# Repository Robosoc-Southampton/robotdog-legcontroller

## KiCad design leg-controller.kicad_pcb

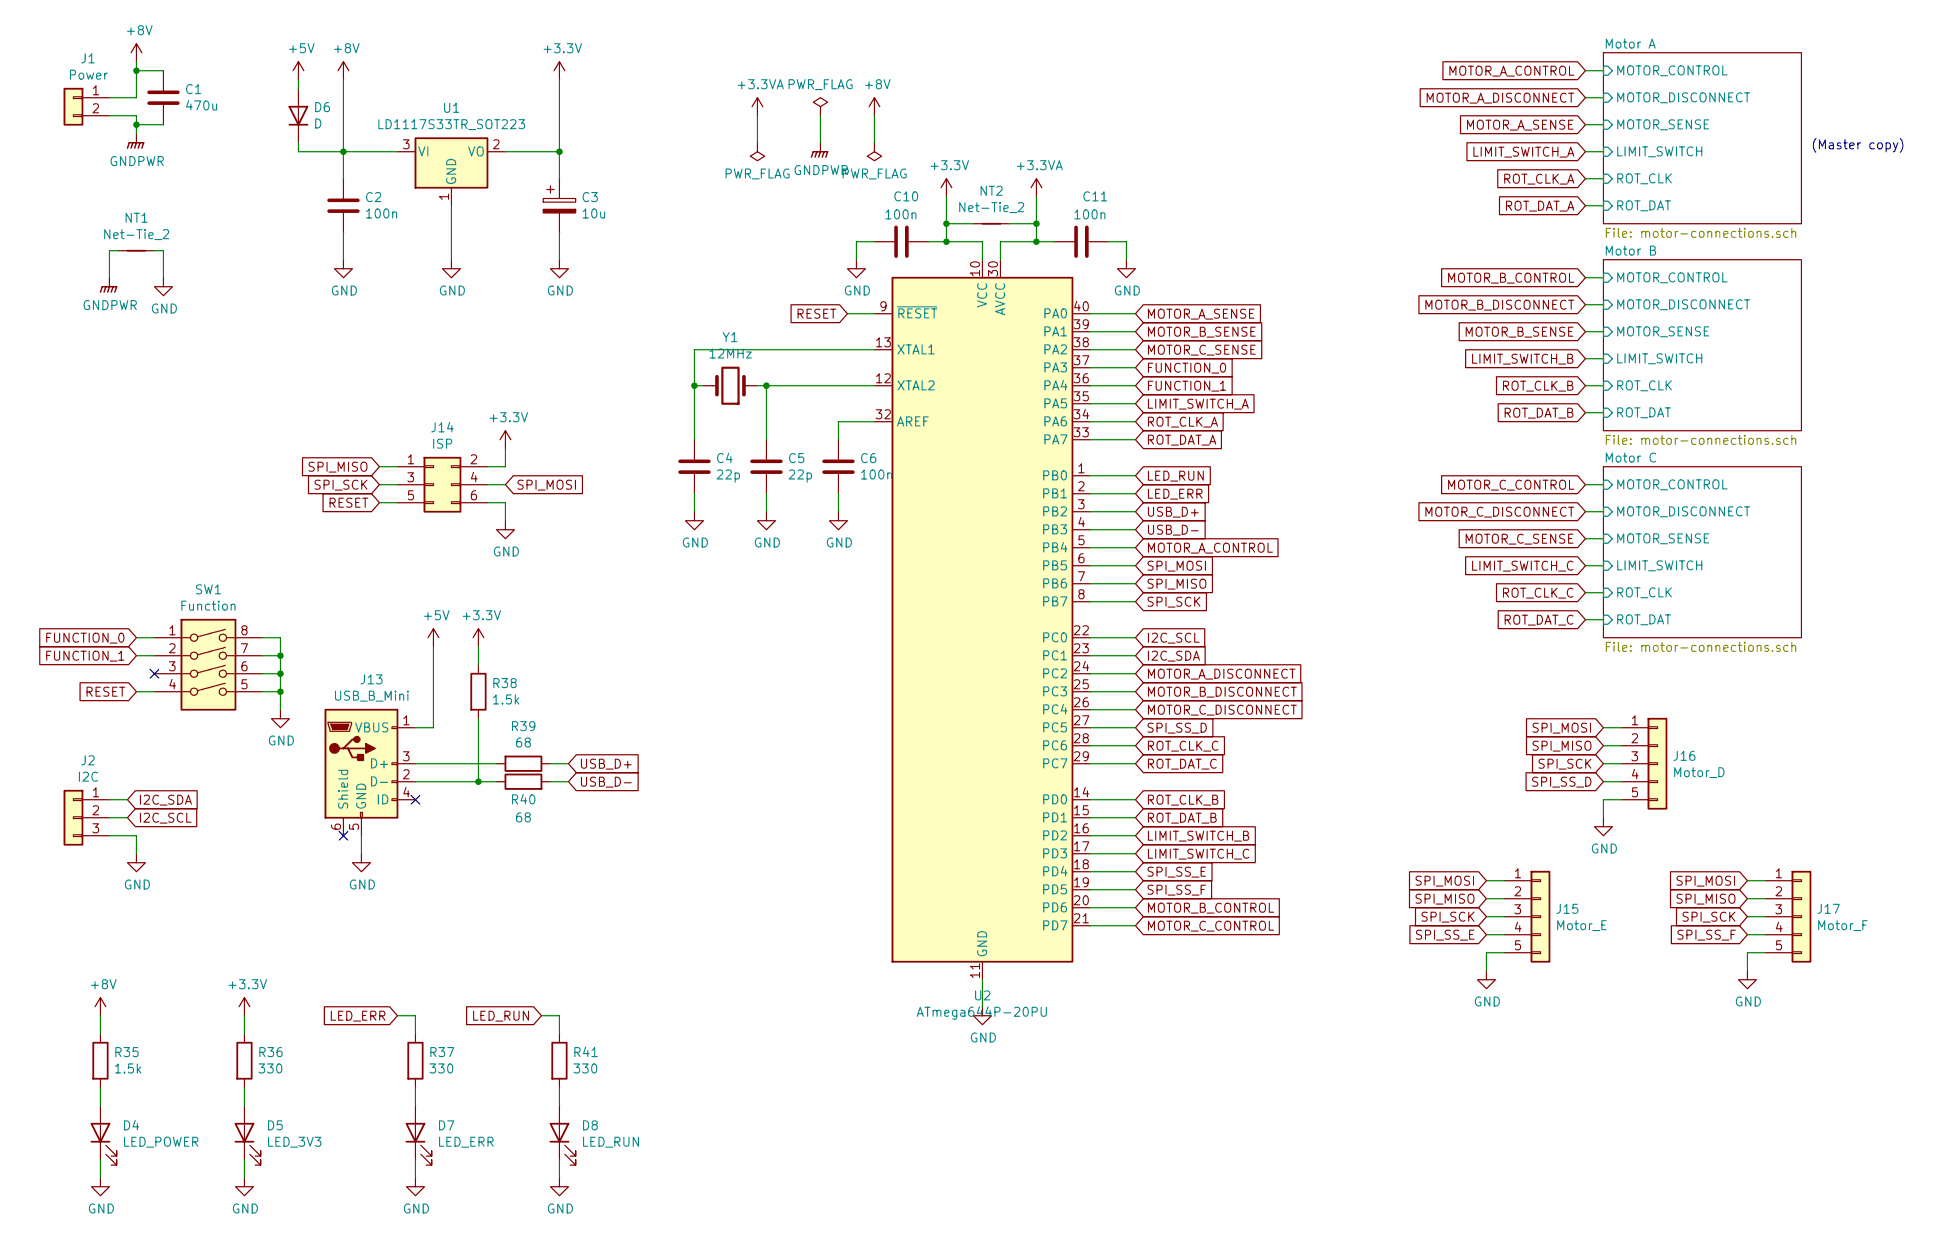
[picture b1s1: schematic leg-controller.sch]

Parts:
C1: 470u; CP_Radial_D10.0mm_P5.00mm
C2: 100n; C_0603_1608Metric_Pad1.08x0.95mm_HandSolder
C3: 10u; CP_Radial_D5.0mm_P2.00mm
C4, C5: 22p; C_0603_1608Metric_Pad1.05x0.95mm_HandSolder
C6, C10, C11: 100n; C_0603_1608Metric_Pad1.05x0.95mm_HandSolder
D4: LED_POWER; LED_0603_1608Metric_Pad1.05x0.95mm_HandSolder
D5: LED_3V3; LED_0603_1608Metric_Pad1.05x0.95mm_HandSolder
D6: D; D_SOD-123F
D7: LED_ERR; LED_0603_1608Metric_Pad1.05x0.95mm_HandSolder
D8: LED_RUN; LED_0603_1608Metric_Pad1.05x0.95mm_HandSolder
J1: Power; TerminalBlock_Altech_AK300-2_P5.00mm
J2: I2C; PinHeader_1x03_P2.54mm_Vertical
J13: USB_B_Mini; USB_Mini-B_Wuerth_65100516121_Horizontal
J14: ISP; PinHeader_2x03_P2.54mm_Vertical
J15: Motor_E; PinHeader_1x05_P2.54mm_Vertical
J16: Motor_D; PinHeader_1x05_P2.54mm_Vertical
J17: Motor_F; PinHeader_1x05_P2.54mm_Vertical
NT1, NT2: Net-Tie_2; NetTie-2_THT_Pad1.0mm
R35, R38: 1.5k; R_0603_1608Metric
R36, R37, R41: 330; R_0603_1608Metric
R39, R40: 68; R_0603_1608Metric
SW1: Function; SW_DIP_SPSTx04_Slide_9.78x12.34mm_W7.62mm_P2.54mm
U1: LD1117S33TR_SOT223; SOT-223-3_TabPin2
U2: ATmega644P-20PU; DIP-40_W15.24mm
Y1: 12MHz; Crystal_SMD_5032-4Pin_5.0x3.2mm

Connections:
+3.3VA: C11.2, NT2.2, U2.30 (AVCC)
+5V: D6.2 (A), J13.1 (VBUS)
+8V: C1.1, C2.1, D6.1 (K), J1.1, R35.1, U1.3 (VI); also elsewhere on the board
FUNCTION_0: SW1.1, U2.37 (PA3)
FUNCTION_1: SW1.2, U2.36 (PA4)
GND: C2.2, C3.2, C4.2, C5.2, C6.2, C10.2, C11.1, D4.1 (K), D5.1 (K), D7.1 (K), D8.1 (K), J2.3, J13.5 (GND), J14.6, J15.5, J16.5, J17.5, NT1.2, SW1.5, SW1.6, SW1.7, SW1.8, U1.1 (GND), U2.11 (GND), U2.31 (GND); also elsewhere on the board
GNDPWR: C1.2, J1.2, NT1.1; also elsewhere on the board
I2C_SCL: J2.2, U2.22 (PC0)
I2C_SDA: J2.1, U2.23 (PC1)
LED_ERR: R37.1, U2.2 (PB1)
LED_RUN: R41.1, U2.1 (PB0)
LIMIT_SWITCH_A: U2.35 (PA5); also elsewhere on the board
LIMIT_SWITCH_B: U2.16 (PD2); also elsewhere on the board
LIMIT_SWITCH_C: U2.17 (PD3); also elsewhere on the board
MOTOR_A_CONTROL: U2.5 (PB4); also elsewhere on the board
MOTOR_A_DISCONNECT: U2.24 (PC2); also elsewhere on the board
MOTOR_A_SENSE: U2.40 (PA0); also elsewhere on the board
MOTOR_B_CONTROL: U2.20 (PD6); also elsewhere on the board
MOTOR_B_DISCONNECT: U2.25 (PC3); also elsewhere on the board
MOTOR_B_SENSE: U2.39 (PA1); also elsewhere on the board
MOTOR_C_CONTROL: U2.21 (PD7); also elsewhere on the board
MOTOR_C_DISCONNECT: U2.26 (PC4); also elsewhere on the board
MOTOR_C_SENSE: U2.38 (PA2); also elsewhere on the board
unnamed: C4.1, U2.13 (XTAL1), Y1.2
unnamed: C5.1, U2.12 (XTAL2), Y1.1
unnamed: C6.1, U2.32 (AREF)
unnamed: D4.2 (A), R35.2
unnamed: D5.2 (A), R36.2
unnamed: D7.2 (A), R37.2
unnamed: D8.2 (A), R41.2
unnamed: J13.2 (D-), R38.2, R40.1
unnamed: J13.3 (D+), R39.2
RESET: J14.5, SW1.4, U2.9 (~RESET)
ROT_CLK_A: U2.34 (PA6); also elsewhere on the board
ROT_CLK_B: U2.14 (PD0); also elsewhere on the board
ROT_CLK_C: U2.28 (PC6); also elsewhere on the board
ROT_DAT_A: U2.33 (PA7); also elsewhere on the board
ROT_DAT_B: U2.15 (PD1); also elsewhere on the board
ROT_DAT_C: U2.29 (PC7); also elsewhere on the board
SPI_MISO: J14.1, J15.2, J16.2, J17.2, U2.7 (PB6)
SPI_MOSI: J14.4, J15.1, J16.1, J17.1, U2.6 (PB5)
SPI_SCK: J14.3, J15.3, J16.3, J17.3, U2.8 (PB7)
SPI_SS_D: J16.4, U2.27 (PC5)
SPI_SS_E: J15.4, U2.18 (PD4)
SPI_SS_F: J17.4, U2.19 (PD5)
USB_D+: R39.1, U2.3 (PB2)
USB_D-: R40.2, U2.4 (PB3)

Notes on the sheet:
(Master copy)

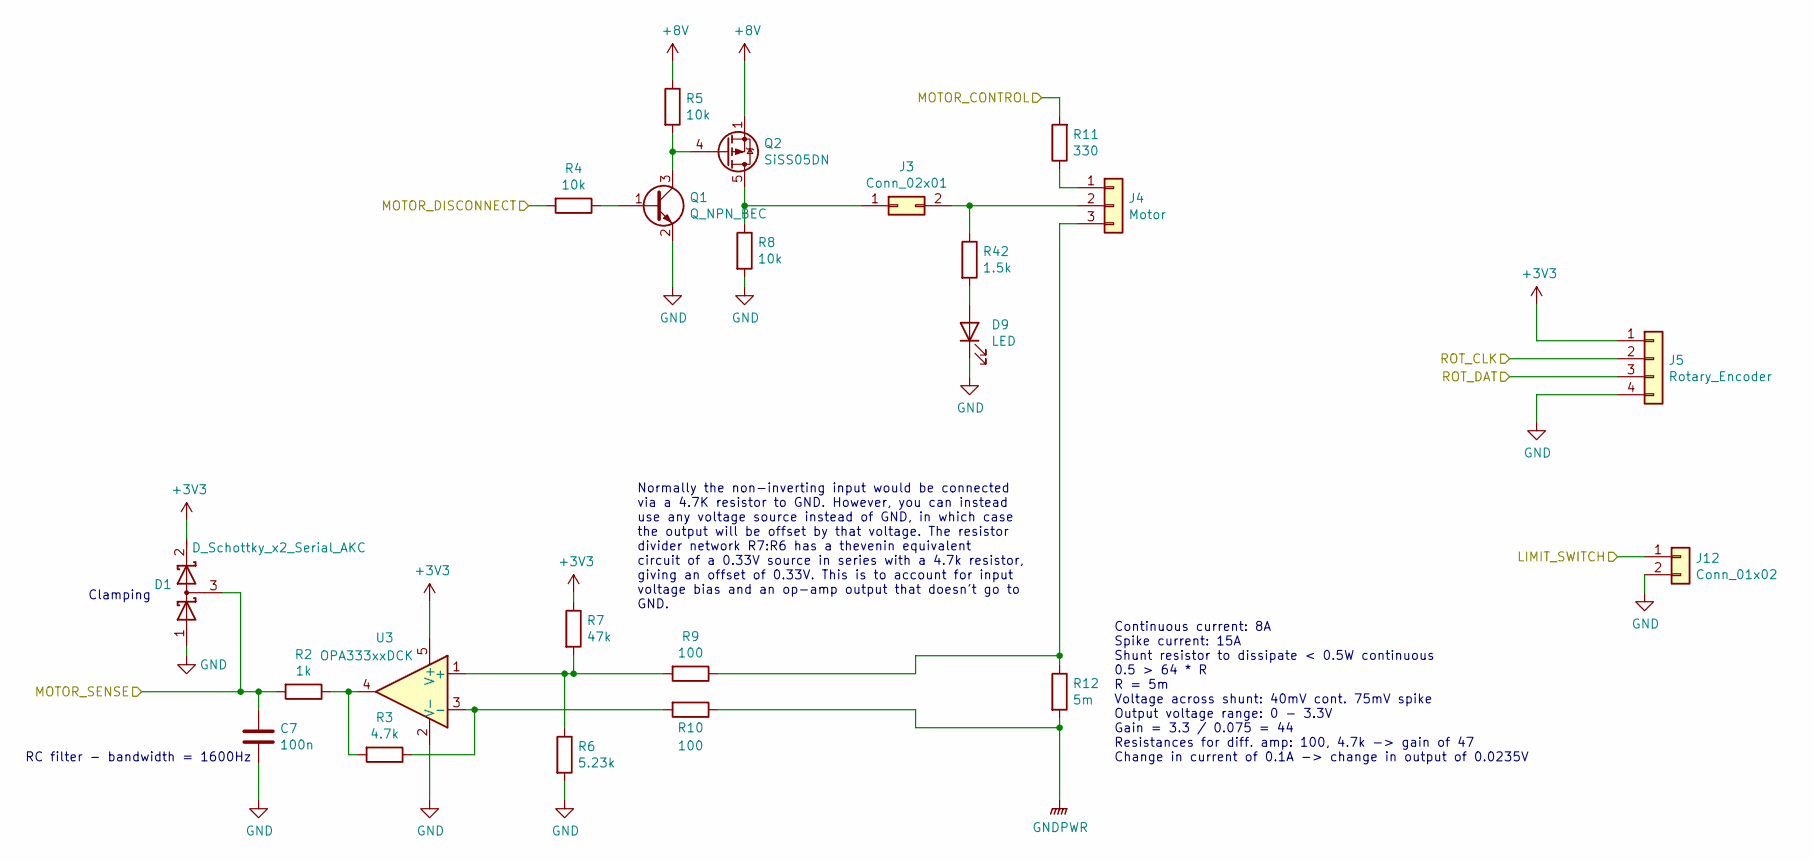
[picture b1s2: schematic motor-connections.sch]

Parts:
C7: 100n; C_0603_1608Metric_Pad1.05x0.95mm_HandSolder
D1: D_Schottky_x2_Serial_AKC; SOT-323_SC-70
D10: LED; LED_0603_1608Metric_Pad1.05x0.95mm_HandSolder
J3: Conn_02x01; PinHeader_1x02_P2.54mm_Vertical
J4: Motor; PinHeader_1x03_P2.54mm_Vertical
J5: Rotary_Encoder; PinHeader_1x04_P2.54mm_Vertical
J12: Conn_01x02; PinHeader_1x02_P2.54mm_Vertical
Q1: Q_NPN_BEC; SOT-23
Q2: SiSS05DN; Vishay_PowerPAK_1212-8_Single
R2: 1k; R_0603_1608Metric
R3: 4.7k; R_0603_1608Metric
R4, R5, R8: 10k; R_0603_1608Metric
R6: 5.23k; R_0603_1608Metric
R7: 47k; R_0603_1608Metric
R9, R10: 100; R_0603_1608Metric
R11: 330; R_0603_1608Metric
R12: 5m; R_2512_6332Metric
R43: 1.5k; R_0603_1608Metric
U3: OPA333xxDCK; SOT-353_SC-70-5_Handsoldering

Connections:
+8V: Q2.1 (S), Q2.2 (S), Q2.3 (S), R5.1; also elsewhere on the board
GND: C7.2, D1.1 (A), D10.1 (K), J5.4, J12.2, Q1.2 (E), R6.2, R8.2, U3.2 (V-); also elsewhere on the board
GNDPWR: R10.1, R12.2; also elsewhere on the board
LIMIT_SWITCH_A: J12.1; also elsewhere on the board
MOTOR_A_CONTROL: R11.2; also elsewhere on the board
MOTOR_A_DISCONNECT: R4.2; also elsewhere on the board
MOTOR_A_SENSE: C7.1, D1.3 (common), R2.2; also elsewhere on the board
unnamed: D10.2 (A), R43.2
unnamed: J3.1, Q2.5 (D), R8.1
unnamed: J4.1, R11.1
unnamed: J4.3, R9.1, R12.1
unnamed: Q1.1 (B), R4.1
unnamed: Q1.3 (C), Q2.4 (G), R5.2
unnamed: R2.1, R3.2, U3.4
unnamed: R6.1, R7.2, R9.2, U3.1 (+)
unnamed: R3.1, R10.2, U3.3 (-)
ROT_CLK_A: J5.2; also elsewhere on the board
ROT_DAT_A: J5.3; also elsewhere on the board

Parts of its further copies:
C8, C9: 100n; C_0603_1608Metric_Pad1.05x0.95mm_HandSolder
D2, D3: D_Schottky_x2_Serial_AKC; SOT-323_SC-70
D9, D11: LED; LED_0603_1608Metric_Pad1.05x0.95mm_HandSolder
J6, J9: Conn_02x01; PinHeader_1x02_P2.54mm_Vertical
J7, J10: Motor; PinHeader_1x03_P2.54mm_Vertical
J8, J11: Rotary_Encoder; PinHeader_1x04_P2.54mm_Vertical
J18, J19: Conn_01x02; PinHeader_1x02_P2.54mm_Vertical
Q3, Q5: Q_NPN_BEC; SOT-23
Q4, Q6: SiSS05DN; Vishay_PowerPAK_1212-8_Single
R13, R24: 1k; R_0603_1608Metric
R14, R25: 4.7k; R_0603_1608Metric
R15, R16, R19, R26, R27, R30: 10k; R_0603_1608Metric
R17, R28: 5.23k; R_0603_1608Metric
R18, R29: 47k; R_0603_1608Metric
R20, R21, R31, R32: 100; R_0603_1608Metric
R22, R33: 330; R_0603_1608Metric
R23, R34: 5m; R_2512_6332Metric
R42, R44: 1.5k; R_0603_1608Metric
U4, U5: OPA333xxDCK; SOT-353_SC-70-5_Handsoldering

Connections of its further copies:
+8V: Q4.1 (S), Q4.2 (S), Q4.3 (S), Q6.1 (S), Q6.2 (S), Q6.3 (S), R16.1, R27.1; also elsewhere on the board
GND: C8.2, C9.2, D2.1 (A), D3.1 (A), D9.1 (K), D11.1 (K), J8.4, J11.4, J18.2, J19.2, Q3.2 (E), Q5.2 (E), R17.2, R19.2, R28.2, R30.2, U4.2 (V-), U5.2 (V-); also elsewhere on the board
GNDPWR: R21.1, R23.2, R32.1, R34.2; also elsewhere on the board
LIMIT_SWITCH_B: J19.1; also elsewhere on the board
LIMIT_SWITCH_C: J18.1; also elsewhere on the board
MOTOR_B_CONTROL: R22.2; also elsewhere on the board
MOTOR_B_DISCONNECT: R15.2; also elsewhere on the board
MOTOR_B_SENSE: C8.1, D2.3 (common), R13.2; also elsewhere on the board
MOTOR_C_CONTROL: R33.2; also elsewhere on the board
MOTOR_C_DISCONNECT: R26.2; also elsewhere on the board
MOTOR_C_SENSE: C9.1, D3.3 (common), R24.2; also elsewhere on the board
unnamed: D9.2 (A), R42.2
unnamed: D11.2 (A), R44.2
unnamed: J6.1, Q4.5 (D), R19.1
unnamed: J7.1, R22.1
unnamed: J7.3, R20.1, R23.1
unnamed: J9.1, Q6.5 (D), R30.1
unnamed: J10.1, R33.1
unnamed: J9.2, J10.2, R44.1
unnamed: J10.3, R31.1, R34.1
unnamed: Q3.1 (B), R15.1
unnamed: Q3.3 (C), Q4.4 (G), R16.2
unnamed: Q5.1 (B), R26.1
unnamed: Q5.3 (C), Q6.4 (G), R27.2
unnamed: R13.1, R14.2, U4.4
unnamed: R14.1, R21.2, U4.3 (-)
unnamed: R17.1, R18.2, R20.2, U4.1 (+)
unnamed: R24.1, R25.2, U5.4
unnamed: R25.1, R32.2, U5.3 (-)
unnamed: R28.1, R29.2, R31.2, U5.1 (+)
ROT_CLK_B: J8.2; also elsewhere on the board
ROT_CLK_C: J11.2; also elsewhere on the board
ROT_DAT_B: J8.3; also elsewhere on the board
ROT_DAT_C: J11.3; also elsewhere on the board

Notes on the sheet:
Normally the non-inverting input would be connected via a 4.7K resistor to GND. However, you can instead use any voltage source instead of GND, in which case the output will be offset by that voltage. The resistor divider network R7:R6 has a thevenin equivalent circuit of a 0.33V source in series w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
Clamping
RC filter - bandwidth = 1600Hz
Continuous current: 8A Spike current: 15A Shunt resistor to dissipate < 0.5W continuous 0.5 > 64 * R R = 5m Voltage across shunt: 40mV cont. 75mV spike Output voltage range: 0 - 3.3V Gain = 3.3 / 0.075 = 44 Resistances for diff. amp: 100, 4.7k -> gain of 47 Change in current of 0.1A -> change in ou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

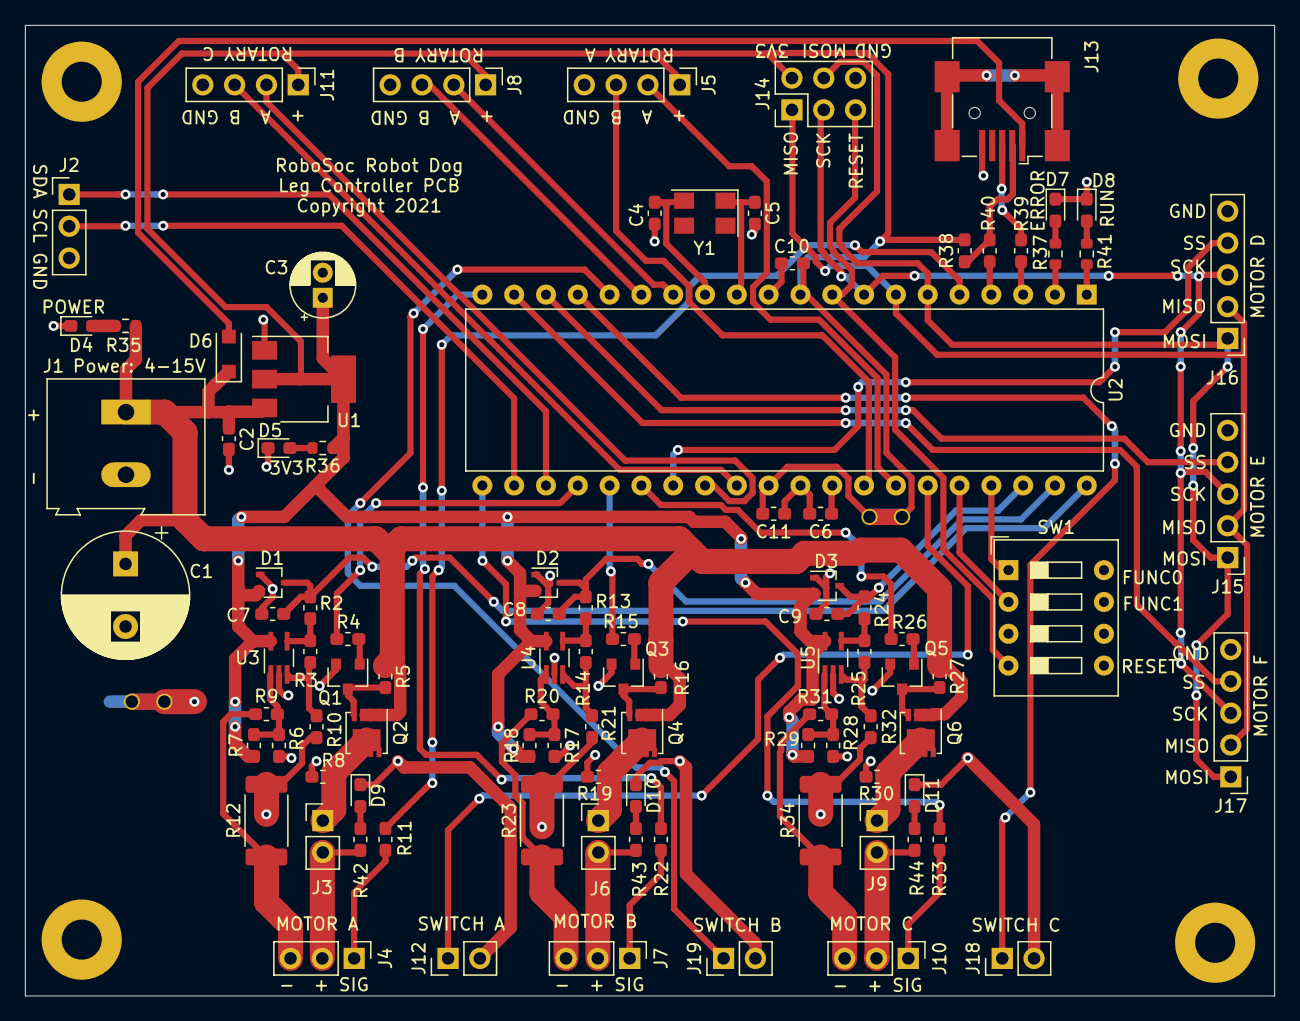
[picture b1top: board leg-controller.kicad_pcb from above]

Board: 2 copper layers, 99.8 x 77.5 mm, 99 parts (0 on the bottom side), 78 nets.

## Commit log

2021-10-31 Added values to some components
2021-11-08 Various changes.
2021-11-10 Added simulation of amplifier
2021-11-10 Fixed amplifier circuit and did some rearranging
2021-11-13 Various changes
2021-11-17 Assigned footprints
2021-11-19 Assigned remaining footprints
2021-11-19 Started workin on PCB layout. A bit faulty...
2021-11-19 Maybe fixed issue?
2021-11-26 First draft of a pcb layout
2021-12-05 Placed components on the PCB
2021-12-09 First draft of the leg controller PCB
2021-12-17 Reduced traces on back to make the ground planes denser
2021-12-17 Forgot .pro
2021-12-17 Fixed silkscreen labels
2021-12-17 Added labels for LEDs
2022-05-06 Added python library

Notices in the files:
leg-controller.kicad_pcb:
Copyright 2021
